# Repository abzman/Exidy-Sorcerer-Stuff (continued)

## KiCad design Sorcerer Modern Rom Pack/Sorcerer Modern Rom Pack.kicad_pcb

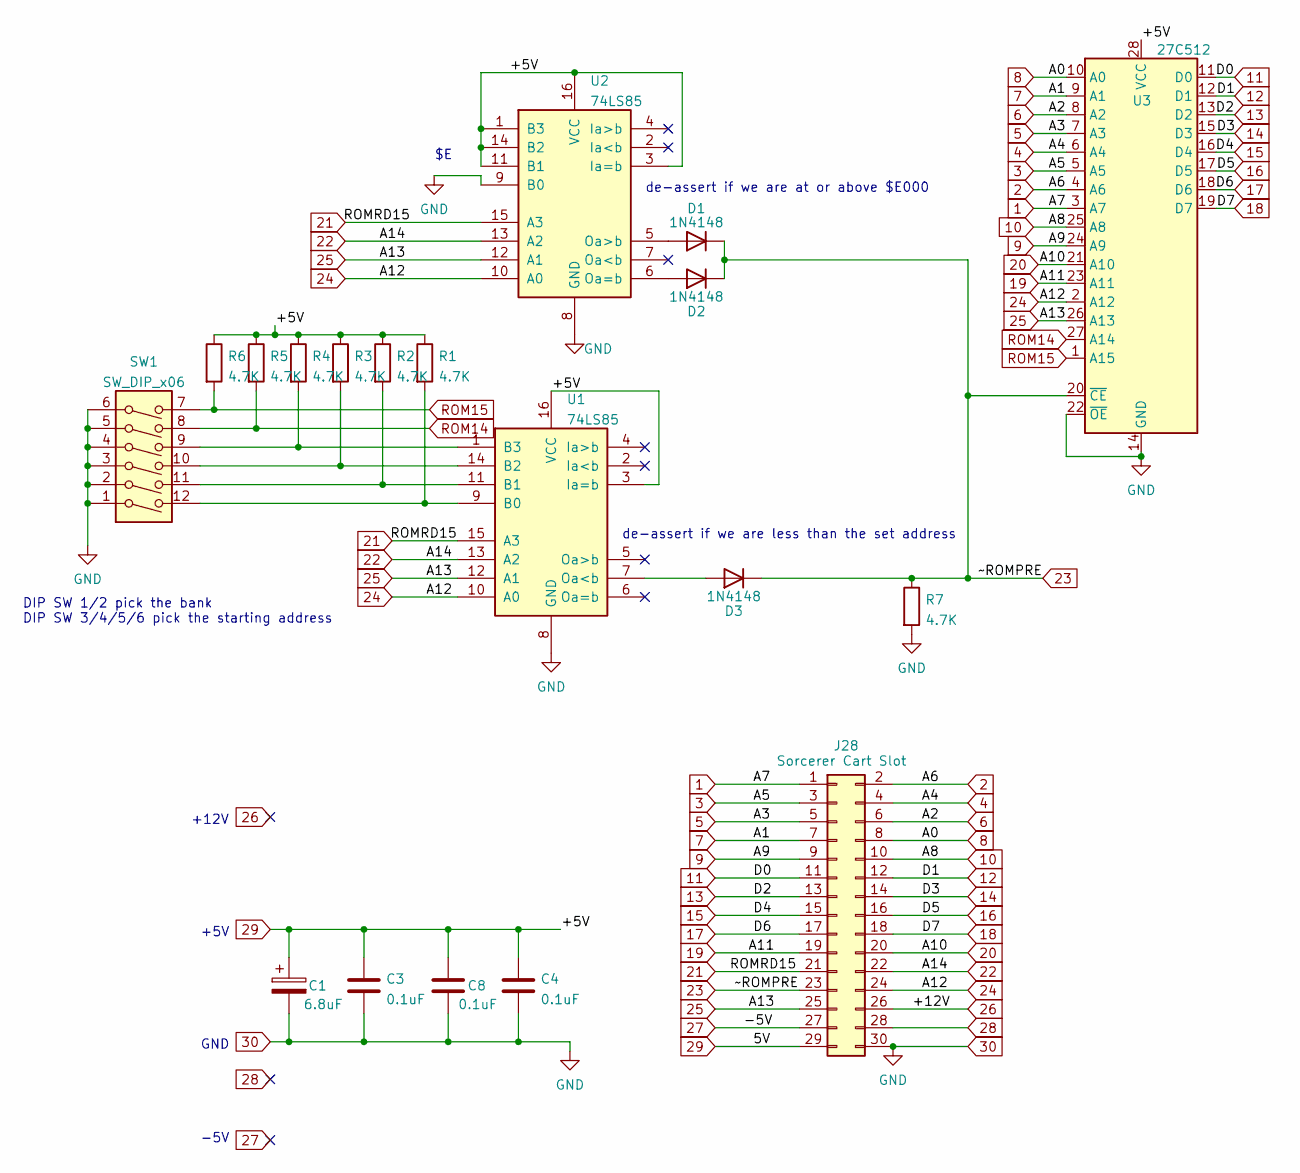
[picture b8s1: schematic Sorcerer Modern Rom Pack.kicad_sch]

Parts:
C1: 6.8uF; CP_Radial_Tantal_D4.5mm_P5.00mm
C3, C4, C8: 0.1uF; C_Disc_D4.3mm_W1.9mm_P5.00mm
D1, D2, D3: 1N4148; D_DO-35_SOD27_P2.54mm_Vertical_KathodeUp
J28: Sorcerer Cart Slot; edge mounted 30 pin card edge connector (2x15 pin)
R1, R2, R3, R4, R5, R6, R7: 4.7K; R_Axial_DIN0204_L3.6mm_D1.6mm_P1.90mm_Vertical
SW1: SW_DIP_x06; SW_DIP_SPSTx06_Piano_10.8x16.8mm_W7.62mm_P2.54mm
U1, U2: 74LS85; DIP-16_W7.62mm
U3: 27C512; DIP-28_W15.24mm

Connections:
1: J28.1, U3.3 (A7)
2: J28.2, U3.4 (A6)
3: J28.3, U3.5 (A5)
4: J28.4, U3.6 (A4)
5: J28.5, U3.7 (A3)
6: J28.6, U3.8 (A2)
7: J28.7, U3.9 (A1)
8: J28.8, U3.10 (A0)
9: J28.9, U3.24 (A9)
10: J28.10, U3.25 (A8)
11: J28.11, U3.11 (D0)
12: J28.12, U3.12 (D1)
13: J28.13, U3.13 (D2)
14: J28.14, U3.15 (D3)
15: J28.15, U3.16 (D4)
16: J28.16, U3.17 (D5)
17: J28.17, U3.18 (D6)
18: J28.18, U3.19 (D7)
19: J28.19, U3.23 (A11)
20: J28.20, U3.21 (A10)
21: J28.21, U1.15 (A3), U2.15 (A3)
22: J28.22, U1.13 (A2), U2.13 (A2)
23: D1.1 (K), D2.1 (K), D3.1 (K), J28.23, R7.1, U3.20 (~CE)
24: J28.24, U1.10 (A0), U2.10 (A0), U3.2 (A12)
25: J28.25, U1.12 (A1), U2.12 (A1), U3.26 (A13)
26: J28.26
27: J28.27
28: J28.28
29: C1.1, C3.1, C4.1, C8.1, J28.29, R1.1, R2.1, R3.1, R4.1, R5.1, R6.1, U1.3 (Ia=b), U1.16 (VCC), U2.1 (B3), U2.3 (Ia=b), U2.11 (B1), U2.14 (B2), U2.16 (VCC), U3.28 (VCC)
30: C1.2, C3.2, C4.2, C8.2, J28.30, R7.2, SW1.1, SW1.2, SW1.3, SW1.4, SW1.5, SW1.6, U1.8 (GND), U2.8 (GND), U2.9 (B0), U3.14 (GND), U3.22 (~OE)
unnamed: D1.2 (A), U2.5 (Oa>b)
unnamed: D2.2 (A), U2.6 (Oa=b)
unnamed: D3.2 (A), U1.7 (Oa<b)
unnamed: R1.2, SW1.12, U1.9 (B0)
unnamed: R2.2, SW1.11, U1.11 (B1)
unnamed: R3.2, SW1.10, U1.14 (B2)
unnamed: R4.2, SW1.9, U1.1 (B3)
ROM14: R5.2, SW1.8, U3.27 (A14)
ROM15: R6.2, SW1.7, U3.1 (A15)

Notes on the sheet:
+5V
-5V
de-assert if we are less than the set address
DIP SW 1/2 pick the bank DIP SW 3/4/5/6 pick the starting address
+12V
de-assert if we are at or above $E000
GND

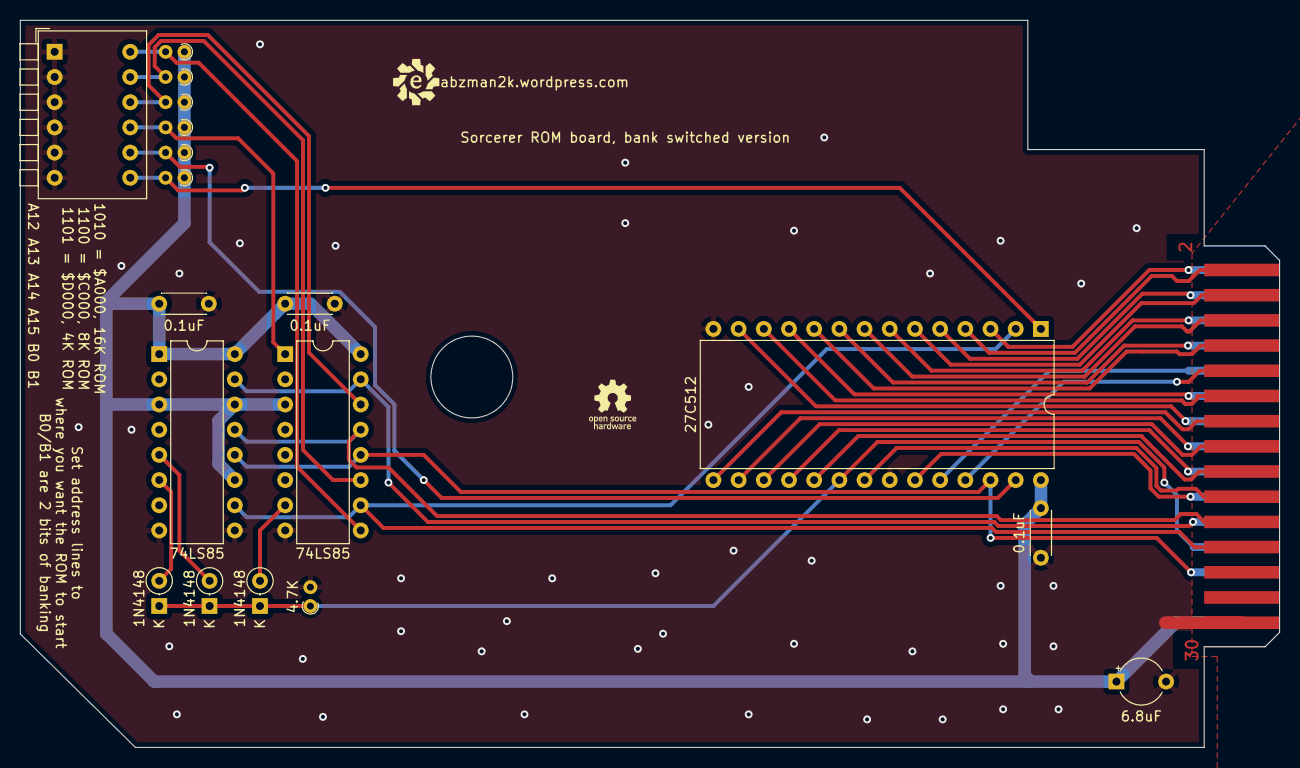
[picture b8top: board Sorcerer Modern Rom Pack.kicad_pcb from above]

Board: 2 copper layers, 127.0 x 73.3 mm, 19 parts (0 on the bottom side), 36 nets.

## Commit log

2022-10-02 added first pass arrington sound and enhanced SMD sound boards
2022-10-02 added arrington eprom programmer
2022-10-04 start on rom pack and updates to sound PCBs
2022-10-14 added rom pak
2022-10-15 many tweaks and experimental silk
2022-10-19 added rom pack extender board
2022-10-22 removed temp files, added gitignore, fixed silk on rom pac board
2022-10-22 internal ram schematic done
2022-10-23 laid out SRAM board
2022-10-23 preliminary schematic for modern rom pack
2022-10-23 tiny schematic change
2022-10-24 silk for bank switched ROM PCB
2022-11-05 Add python script for generating combinations of jumpers
2022-11-12 added gerbers for boards I had made
2022-12-31 Add script to calculate resistor ladder response
2022-12-31 Some corrections to mappings file
2023-05-07 finished card edge breakout
2023-12-13 tweaked board designs
2024-01-18 added 3d models
2024-02-16 added plots of python program
2024-02-16 updated some files to newer kicad
2024-02-16 updated to latest kicad
2024-02-19 updates to be closer to real one
2024-02-19 updated some DRC stuff
2024-02-26 removed outdated gerbers, updated design to version 2
2024-03-28 added ram disk v1.1 layout
2024-03-28 added source for layout of v1.1
2024-04-05 s100 expansion chassis layout first pass done
2024-04-05 tweaks to schematic
2024-04-10 added photo of s100 chassis
2025-04-18 cleaned up things
